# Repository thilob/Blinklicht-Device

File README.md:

# ESP32 Blaulicht-Controller mit Web-UI & CLI

Dieses Projekt ist ein **Blaulicht-Controller für Modellbau und ähnliche Anwendungen**.  
Die Software läuft auf verschiedenen ESP32-Boards und nutzt die jeweils vorhandenen **LEDC-PWM-Kanäle** der Zielhardware.  

---

## Features

- Bis zur **hardwareabhaengigen LEDC-Grenze** des jeweiligen ESP32-Ziels (PWM, 5 kHz, 8 Bit Helligkeit)  
- **Mehrere Blinkmuster (Patterns)**, die frei definierbar sind  
- **Gruppen-Funktion**: LEDs lassen sich zu Gruppen zusammenfassen und gemeinsam ein-/ausschalten  
- **Phasenverschiebung**: gleiche Muster können zeitlich versetzt starten  
- **Weboberfläche (GUI)**: läuft direkt im Browser (Handy, Tablet, PC), responsive gestaltet  
- **Serielle Konsole (CLI)**: alle Funktionen auch über USB-Terminal steuerbar  
- **Speicherung im Flash** (LittleFS): Konfiguration überlebt Neustarts  
- **WLAN-Betrieb**: Access Point (AP) oder Station (STA, DHCP) mit mDNS (z. B. `http://blaulicht-xxxx.local`)  
- **Captive Portal**: Im AP-Modus wird die Weboberfläche automatisch geöffnet  
- **Brownout-Schutz**: externe Kondensatoren empfohlen (siehe unten)  

---

## Hardware-Aufbau

### ESP32-DevKit
- Verwendet wird ein Standard-ESP32-DevKit (mit USB-Anschluss und Spannungsregler).  

### LED-Ausgänge
- PWM ist nicht auf "ein paar Spezialpins" begrenzt, sondern kann auf viele ausgabefaehige GPIOs gemappt werden.  
- Die eigentliche Grenze ist die Anzahl gleichzeitig verfuegbarer **LEDC-Kanaele** der jeweiligen ESP32-Variante.  
- Das Projekt begrenzt die Standard-Konfiguration automatisch auf die LEDC-Kapazitaet der gewaehlten Zielhardware.  
- Jeder Ausgang steuert eine LED oder LED-Baugruppe.  
- Vor jede LED gehört ein **Vorwiderstand** (typisch 220–470 Ω bei 5 V Betrieb).  

### Versorgung & Brownout-Schutz
Der ESP32 ist empfindlich gegenüber Spannungseinbrüchen („Brownout“).  
Das passiert besonders dann, wenn mehrere LEDs gleichzeitig leuchten oder wenn das WLAN viel Strom zieht.

👉 Deshalb unbedingt folgende Maßnahmen:
- **Ein großer Elektrolytkondensator** (470 µF bis 1000 µF, 6,3 V oder mehr) **zwischen 3,3 V und GND**, möglichst nah am ESP32 bzw. am `3V3`-Pin des Devkits.  
- **Ein Keramikkondensator** (100 nF) direkt am Board bzw. an `3V3`/`GND` als schnelle Stütze.  
- Wenn die Schaltung über USB versorgt wird und die LED-Last die `5V`-Schiene stark belastet, zusätzlich ein weiterer Elko **zwischen `USB 5V` und `GND`** nahe am Devkit oder an der Last.  

So werden Spannungsschwankungen abgefangen und der ESP32 läuft stabil.

---

## Schaltplan (vereinfacht)

### Prinzipdarstellung (ASCII)

```  
USB 5V ----+-----------------------------+
           |                             |
      [DevKit-Regler 3.3V]               |
           |                             |
          3V3 ---+---- ESP32             |
                 |      +-----+-----+    |
             [470uF]    |           |    |
                 |  GPIOx       GPIOy ...|
                GND  |            |      |
                    [R]          [R]     |
                     |            |      |
                    LED          LED     |
                     |            |      |
GND -----------------+------------+------+

Optional bei hoher LED-Last auf USB/5V:

USB 5V ---+--- [zus. Elko 470uF..1000uF] --- GND
```

- `[R]` = Vorwiderstand (220–470 Ω)  
- `[470uF]` = Pufferkondensator zwischen `3.3V` und `GND` gegen Brownouts  
- `[zus. Elko 470uF..1000uF]` = optionaler Puffer zwischen `USB 5V` und `GND`, wenn die `5V`-Versorgung durch LED-Last stark einbricht  

---

## Software-Prinzip

### Patterns (Blinkmuster)
Ein **Pattern** ist eine Liste von Schritten:
- `duration_ms` – Dauer in Millisekunden  
- `level` – Ziel-Helligkeit (0..255)  
- `fade` – weicher Übergang (true) oder harter Sprung (false)  

Beispiel für ein Doppelblitz-Pattern:

```cpp
{30, 255, false},  // LED an
{30,   0, false},  // aus
{30, 255, false},  // LED an
{150, 0,  true},   // langsam ausblenden
{250, 0,  false},  // Pause
```

- Der **letzte Schritt ist die Pause**, bevor das Muster neu startet.  
- Pro Ausgang kann das Pattern individuell gewählt werden.  
- Jeder Ausgang kann zusätzlich eine **Zusatzpause** bekommen, die auf den letzten Schritt des Patterns aufaddiert wird.  

### Gruppen
- Mehrere Ausgänge können zu **Gruppen** zusammengefasst werden.  
- Eine Gruppe kann komplett **ein- oder ausgeschaltet** werden.  
- Ist eine Gruppe aus, bleiben die LEDs dunkel (das Pattern pausiert).  

---

## CLI (Serielle Konsole)

Über USB (115200 Baud) öffnet sich ein Terminal.  
Man sieht, was man tippt (Echo-Funktion ist aktiv).

### Wichtige Befehle:

- `help` → alle Befehle anzeigen  
- `status` → Status von WLAN, Patterns, Gruppen und Ausgängen  
- `wifi on|off` → WLAN/Webserver ein-/ausschalten  
- `mode ap|sta` → WLAN-Modus wählen  
- `sta <ssid> <pass>` → Zugangsdaten für Station-Modus setzen  
- `ap <ssid> [pass]` → SSID/PW für Access Point setzen  
- `dhcp` → im STA-Modus neue DHCP-Adresse beziehen  
- `pat list` → Patterns anzeigen  
- `pat add <name>` → neues Pattern anlegen  
- `pat step add <pidx> <dur> <lvl> <fade>` → Step zu Pattern hinzufügen  
- `group list` → Gruppen anzeigen  
- `group add <id> <name>` → Gruppe anlegen  
- `light list` → Ausgänge anzeigen  
- `light add <pin> <ch> <pidx> <zusatzpause> <gid> <phase>` → Ausgang hinzufügen  

---

## Weboberfläche (GUI)

Die **Web-UI** wird aus dem Flash geladen (`LittleFS`).  
- Im AP-Modus erreichbar unter: `http://192.168.4.1`  
  (Captive Portal öffnet die Seite oft automatisch)  
- Im STA-Modus unter: `http://<hostname>.local` oder über die vergebene DHCP-IP  

### Funktionen:
- WLAN konfigurieren (AP oder STA)  
- Patterns anlegen, bearbeiten, löschen  
- Gruppen verwalten und schalten  
- Ausgänge (Lights) hinzufügen, ändern, löschen  

Die Oberfläche ist **responsive** (Bootstrap-Layout) → funktioniert gut auf Handy, Tablet und PC.  

---

## Build & Flash (PlatformIO)

1. Projekt in **VS Code / PlatformIO** öffnen  
2. **Build** → Firmware kompilieren  
3. **Upload** → ESP32 flashen  
4. **Upload Filesystem Image** → Weboberfläche (index.html) ins LittleFS laden  
5. Serielle Konsole (115200 Baud) starten → Logausgaben prüfen  

### CLI-Beispiele

```bash
# Firmware für ESP32 DevKit V1 / ESP32-WROOM bauen
$HOME/.platformio/penv/bin/pio run -e devkit-v1

# Firmware hochladen
$HOME/.platformio/penv/bin/pio run -e devkit-v1 -t upload

# LittleFS-Image hochladen
$HOME/.platformio/penv/bin/pio run -e devkit-v1 -t uploadfs
```

### Upload-Port / udev-Hinweise unter Linux

Beim Upload kann PlatformIO z. B. folgende Meldungen anzeigen:

```text
Looking for upload port...

Warning! Please install `99-platformio-udev.rules`.
More details: https://docs.platformio.org/en/latest/core/installation/udev-rules.html

Auto-detected: /dev/ttyS0
Uploading .pio/build/devkit-v1/littlefs.bin
esptool.py v4.11.0
Serial port /dev/ttyS0
```

Das bedeutet meist:
- Die empfohlenen PlatformIO-`udev`-Regeln für USB-Seriell-Geräte sind noch nicht installiert.
- PlatformIO hat vermutlich den falschen Port erkannt.
- `/dev/ttyS0` ist oft **nicht** der USB-Port des ESP32, sondern eine interne serielle Schnittstelle des PCs.

Prüfe in so einem Fall die tatsächlich vorhandenen USB-Ports, z. B.:

```bash
ls /dev/ttyUSB* /dev/ttyACM* 2>/dev/null
```

Und gib den Upload-Port dann explizit an:

```bash
$HOME/.platformio/penv/bin/pio run -e devkit-v1 -t upload --upload-port /dev/ttyUSB0
$HOME/.platformio/penv/bin/pio run -e devkit-v1 -t uploadfs --upload-port /dev/ttyUSB0
```

Wenn du unter Linux häufiger Upload-Probleme oder Zugriffsfehler auf serielle Geräte hast, installiere die PlatformIO-`udev`-Regeln:
- Doku: https://docs.platformio.org/en/latest/core/installation/udev-rules.html

### Richtigen Port beim Einstecken finden

Wenn unklar ist, welches Device zu deinem ESP32 gehört, öffne vor dem Einstecken ein Kernel-Log:

```bash
journalctl -k -f
```

Alternativ:

```bash
dmesg --follow
```

Stecke dann den ESP32 an. Typische Meldungen nennen danach den neu angelegten Port, z. B.:

```text
cdc_acm 1-1.3:1.0: ttyACM0: USB ACM device
```

oder:

```text
ch341-uart converter now attached to ttyUSB0
```

Diesen Port kannst du anschließend direkt für Upload und Monitor verwenden:

```bash
$HOME/.platformio/penv/bin/pio run -e devkit-v1 -t upload --upload-port /dev/ttyACM0
$HOME/.platformio/penv/bin/pio device monitor --port /dev/ttyACM0 --baud 115200
```

---

## Fazit

Mit diesem Projekt erhältst du eine **flexible Steuerung für Modellbau-Blaulichter**:  
- Komfortabel über **Web-GUI**  
- Alternativ robust über **CLI**  

Dank externer **Pufferkondensatoren** läuft der ESP32 stabil, auch wenn mehrere LEDs gleichzeitig blinken.  
Die Software ist modular aufgebaut und lässt sich leicht erweitern.

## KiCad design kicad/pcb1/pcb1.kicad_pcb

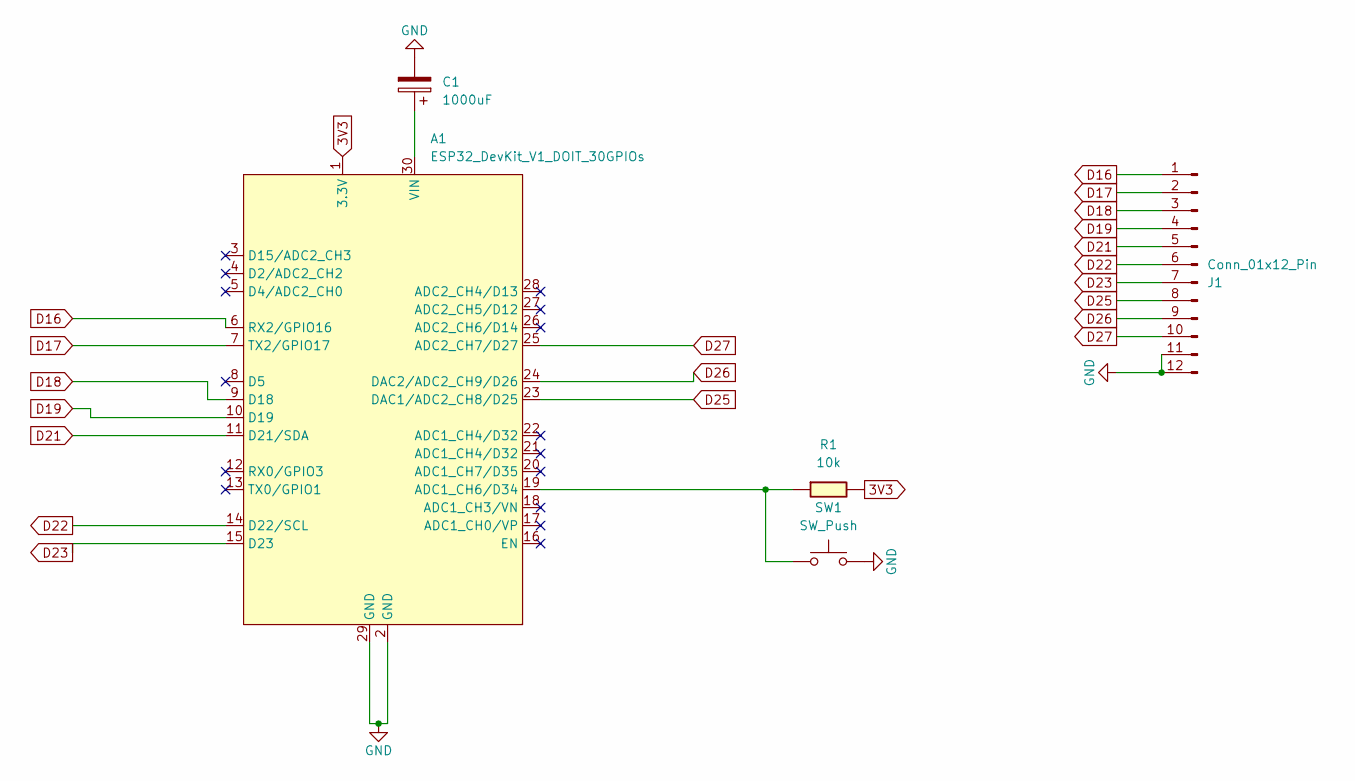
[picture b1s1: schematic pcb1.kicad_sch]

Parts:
A1: ESP32_DevKit_V1_DOIT_30GPIOs; DOIT_ESP32_DEVKIT_30Pins
C1: 1000uF; C_Radial_D10.0mm_H20.0mm_P5.00mm
J1: Conn_01x12_Pin; PinHeader_1x12_P2.54mm_Vertical
R1: 10k; R_1206
SW1: SW_Push; SW_Push_SPST_NO_Alps_SKRK

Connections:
3V3: A1.1 (3.3V), R1.1
D16: A1.6 (RX2/GPIO16), J1.1
D17: A1.7 (TX2/GPIO17), J1.2
D18: A1.9 (D18), J1.3
D19: A1.10 (D19), J1.4
D21: A1.11 (D21/SDA), J1.5
D22: A1.14 (D22/SCL), J1.6
D23: A1.15 (D23), J1.7
D25: A1.23 (DAC1/ADC2_CH8/D25), J1.8
D26: A1.24 (DAC2/ADC2_CH9/D26), J1.9
D27: A1.25 (ADC2_CH7/D27), J1.10
GND: A1.2 (GND), A1.29 (GND), C1.2, J1.11, J1.12, SW1.2
unnamed: A1.19 (ADC1_CH6/D34), R1.2, SW1.1
unnamed: A1.30 (VIN), C1.1

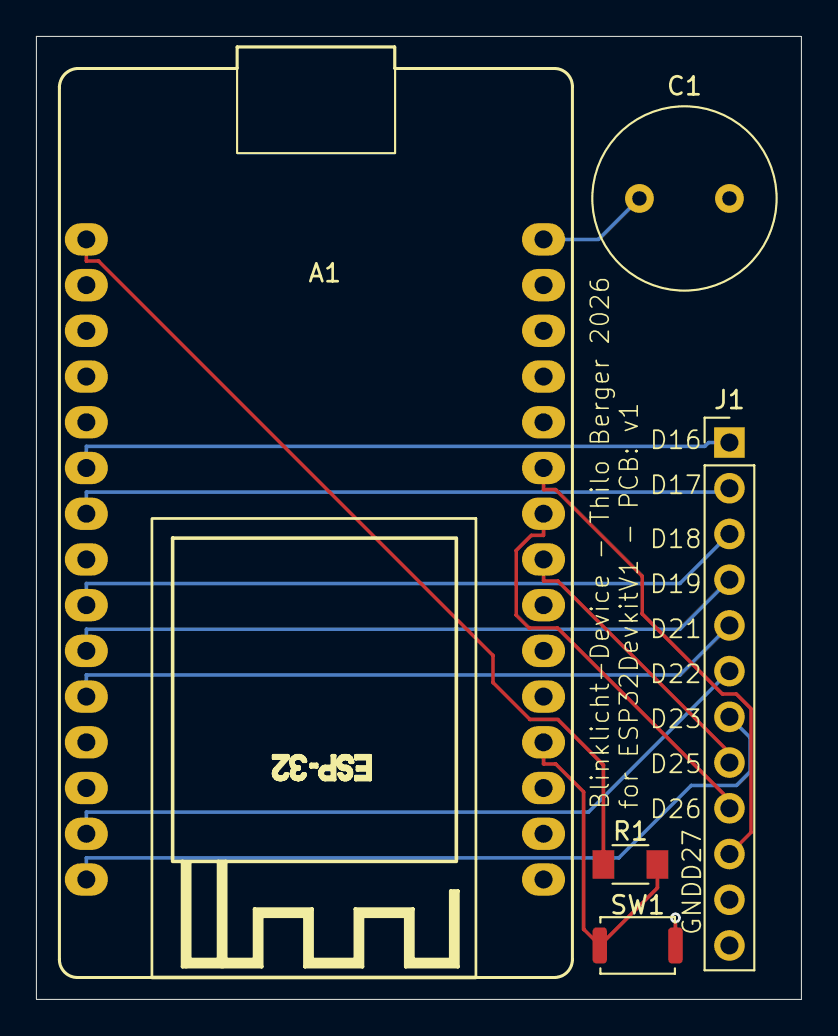
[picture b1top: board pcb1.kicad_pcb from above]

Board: 2 copper layers, 42.5 x 53.5 mm, 5 parts (0 on the bottom side), 14 nets.

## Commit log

2025-09-28 erster Programmentwurf mit einfachem Blinken.
2025-09-28 V2, mit zwei funktionierenden Ausgängen
2025-09-28 v3 Fuktionsfähig mit vier Blaulichtern
2025-09-28 v4 vier Ausgänge mit verschiedenen Pattern
2025-09-28 v5 mit acht Ausgängen und variablen Pattern
2025-09-30 neuer überarbeiteter Zweig.
2025-09-30 korrigierte Main.cpp, so dass keine littlefs-Fehler mehr auftreten sollten.
2025-09-30 lauffähig, Auswahl Accesspoint jetzt möglich.
2025-09-30 CLI-Befehl für DHCP hinzugefügt.
2025-09-30 eindeutiger WLAN-Name wird im AP-Modus erzeugt (MAC-Adresse wird teilweise verwendet)
2025-09-30 erste Version mit Captive Portal im AP-Modus
2025-09-30 Version mit Hardware-Reset an GPIO 32
2025-09-30 vor patch
2025-09-30 neuester funktionierender Zwischenstand
2025-09-30 speichern und ausführen-Funktion so angepasst, dass beim Speichern von nicht-WLAN-Daten kein Neustart oder keine Änderung der WLAN-Daten eintritt.
2025-10-01 verbesserte Readme-Datei und Hilfetexte in der Weboberfläche.
2025-10-01 index.html mit Tooltips versehen
2025-11-29 ESP32C3 aufgenommen.
2025-12-14 vor einführung board config system
2025-12-14 nach einführung board config system
2025-12-14 Anpassungen im Code, um Race Conditions vorzubeugen.
2025-12-14 Überarbeitung zur Brownout-Verhinderung
2026-03-15 Fix PlatformIO board compatibility check
2026-03-31 Add ESP32 DevKit V1 environment and upload docs
2026-03-31 Fix wifi save and apply endpoints
2026-03-31 Remove AI assistance note from README
2026-03-31 Improve mobile responsiveness
2026-04-01 Fix /api/wifi payload parsing
2026-04-01 Auto-increment group IDs in UI
2026-04-01 Make PWM limits hardware-aware
2026-04-01 Rework GUI entity editing and pattern XML
2026-04-01 Add STA hostname hint to GUI
2026-04-01 Add STA reconnect helper window
2026-04-01 Generalize WiFi reconnect helper window
2026-04-01 Show group names for light assignments
2026-04-01 Show memory usage on status page
2026-04-01 Improve status memory visualization
2026-04-01 Polish group and light list UI
2026-04-01 Refine group overview UX
2026-04-01 Fix group toggle persistence
2026-04-01 Stabilize group toggle layout
2026-04-01 Add config backup and footer note
2026-04-01 Rename rest override to extra pause
2026-04-01 Adopt live patterns as defaults
2026-05-09 Kicad-PCB hinzugefügt.
2026-05-10 BOM aufgenommen
2026-05-10 nach Versand an JLCPCB
2026-05-10 added Pin Desc
2026-05-19 anpassung gitignore
